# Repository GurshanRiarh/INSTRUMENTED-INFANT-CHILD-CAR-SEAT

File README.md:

# Instrumented Infant-Child Car Seat — Pressure-Sensitive Mat Hardware

This repository contains the KiCad hardware for the pressure-sensitive mat (PSM)
sub-system of the Carleton University capstone project **Instrumented
Infant-Child Car Seat**.

Two hardware revisions are included:

| Revision | Purpose | Board |
|---|---|---|
| **PSM V1** | Reproduction of Roger Selzler's 2018 thesis PSM (16× VCNL4020, 4×4 array). This is the experimental baseline. | 101.6 × 101.6 mm, 0.2 mm polyimide flex, 2 layers |
| **PSM V3** | Prannav's proposed improvements: VCNL4030X01 sensors, four factory I²C addresses per tile, one mux, modular 2×2 tiles, sealing/waterproofing features. | 4 × 30 × 30 mm flex tiles + 60 × 40 mm FR4 hub |

Both PCB revisions pass KiCad DRC with **0 violations and 0 unconnected
items**. All three schematics pass ERC with **0 violations**. The boards are
research prototypes, not certified medical or automotive devices.

**Interactive board viewer:** open [board-viewer.html](board-viewer.html) in a browser for 3D angled/top/bottom views, 2D copper/silkscreen views, full schematics, and a lightbox.

## Repository map

```
board-viewer.html            self-contained 3D + 2D board viewer
hardware/
  libraries/                 footprints, symbols, and approximate STEP models
  psm-v1/                    thesis-baseline KiCad project (schematic + PCB)
    fab/                     Gerbers, drill, position file, PDF/SVG preview
  psm-v3/
    tile/                    modular 4-sensor tile project (schematic + PCB)
    hub/                     one-mux / four-port hub project (schematic + PCB)
docs/                        architecture, design notes, validation, fabrication, tests
mechanical/                  parametric silicone tile mold (OpenSCAD) + process notes
scripts/                     board/3D/viewer generators, BOM and check helpers
firmware/                    optional I²C bring-up script for a Raspberry Pi
```

## Quick start

1. Install KiCad 9 or newer (this design was validated with **KiCad 10.0.7**).
2. Open one of:
   - `hardware/psm-v1/psm-v1.kicad_pro` — schematic + PCB
   - `hardware/psm-v3/tile/psm-v3-tile.kicad_pro` — sensor tile schematic + PCB
   - `hardware/psm-v3/hub/psm-v3-hub.kicad_pro` — hub schematic + PCB
3. The project-local `fp-lib-table` and `sym-lib-table` load the custom
   footprints/symbols from `hardware/libraries/`.
4. Fabrication data is in each project's `fab/` folder. Review the fab notes
   in [docs/fabrication.md](docs/fabrication.md) before ordering.

Command-line checks:

```bash
kicad-cli pcb drc --severity-all --output drc.rpt hardware/psm-v1/psm-v1.kicad_pcb
kicad-cli sch erc --output erc.rpt hardware/psm-v1/psm-v1.kicad_sch
kicad-cli pcb drc --severity-all --output drc.rpt hardware/psm-v3/tile/psm-v3-tile.kicad_pcb
kicad-cli sch erc --output erc.rpt hardware/psm-v3/tile/psm-v3-tile.kicad_sch
kicad-cli pcb drc --severity-all --output drc.rpt hardware/psm-v3/hub/psm-v3-hub.kicad_pcb
kicad-cli sch erc --output erc.rpt hardware/psm-v3/hub/psm-v3-hub.kicad_sch

# Regenerate the self-contained viewer from the current PCB/schematic files
python3 scripts/build_board_viewer.py
```

## PSM V1 — thesis baseline

The V1 board follows Selzler's thesis:

- 16 × **Vishay VCNL4020** infrared proximity sensors in a 4×4 grid on a
  4-inch-square flexible PCB.
- Two **PCA9548A** 8-channel I²C switches at 0x70 and 0x71. Each VCNL4020 has
  the fixed 7-bit address 0x13, so each sensor gets its own mux channel:
  - U17 channels 0–7 → U1–U8
  - U18 channels 0–7 → U9–U16
- 10 Ω IR-anode series resistors, 100 nF local decoupling per sensor,
  22 µF bulk per mux, 4.7 kΩ upstream I²C pull-ups, 10 kΩ reset/INT pull-ups.
- 2×5, 2.54 mm host header (Tiva/LaunchPad-compatible).
- 25.4 mm sensor pitch, 0.2 mm polyimide flex stack-up, 2 layers.

The editable schematic is `hardware/psm-v1/psm-v1.kicad_sch`; a PDF is at
[docs/psm-v1-schematic.pdf](docs/psm-v1-schematic.pdf).

> **Important:** the thesis does not publish a complete netlist, BOM, or
> mechanical drawing. The V1 design is a reconstruction from the thesis text
> and the Vishay datasheet. Verify the silicone cavity geometry against the
> original before fabrication.

## PSM V3 — modular, serviceable upgrade

V3 implements the improvement points from Prannav's proposal sections:

| Proposal point | Implementation |
|---|---|
| Replace the NRND VCNL4020 | **VCNL4030X01** (AEC-Q101, 16-bit PS, four factory addresses) |
| Reduce mux complexity / improve addressing | One **PCA9548A** (0x70) serves four tile ports; each tile has four sensors at 0x60/0x51/0x40/0x41. One mux supports up to 8 tiles / 32 sensors. |
| Do not restrict the array to 4×4 | Modular **2×2 sensor tiles** (30 × 30 mm) can be placed along the car-seat contour and replaced individually. |
| Waterproofing / infant environment | Sealing-ring guide on `Dwgs.User`, ground ring, via tenting/plugging option, ENIG finish, conformal-coat instructions, sealed connectors. |
| Silicone manufacturing | Parametric vacuum-degassing mold in `mechanical/tile_mold.scad` plus process notes. |
| KiCad design package | Full tile and hub PCB projects, BOM, Gerbers, drill, position files, PDF/SVG previews. |

| V3 tile PCB | V3 hub PCB |
|---|---|
|  |  |

| V3 tile schematic | V3 hub schematic |
|---|---|
|  |  |

The V3 projects include full schematics (`psm-v3-tile.kicad_sch` and
`psm-v3-hub.kicad_sch`), the connection topology diagram, and the routed PCBs.
Schematics are in [docs/psm-v3-tile-schematic.pdf](docs/psm-v3-tile-schematic.pdf)
and [docs/psm-v3-hub-schematic.pdf](docs/psm-v3-hub-schematic.pdf).

## Pinouts and address map

### V1 host header J1 (2×5, 2.54 mm)

| Pin | Net | Pin | Net |
|---:|---|---:|---|
| 1 | 3V3 | 2 | GND |
| 3 | SDA | 4 | SCL |
| 5 | INT_N | 6 | MUX_RST |
| 7 | 5V (optional) | 8 | GND |
| 9 | NC | 10 | NC |

### V1 sensor channel map

| Mux | Address | Channel 0 | 1 | 2 | 3 | 4 | 5 | 6 | 7 |
|---|---|---|---|---|---|---|---|---|---|
| U17 | 0x70 | U1 | U2 | U3 | U4 | U5 | U6 | U7 | U8 |
| U18 | 0x71 | U9 | U10 | U11 | U12 | U13 | U14 | U15 | U16 |

### V1 VCNL4020 pin use

| Pin | Name | Connection |
|---:|---|---|
| 1 | IR anode | 3V3 through 10 Ω; 100 nF to GND |
| 2 | SDA | Mux channel `SDA_Cn` |
| 3 | INT | `INT_N` (open-drain, 10 kΩ pull-up) |
| 4 | SCL | Mux channel `SCL_Cn` |
| 5 | VDD | 3V3; 100 nF to GND |
| 6, 7 | NC | Not connected |
| 8, 9 | GND | GND |
| 10 | IR cathode | Not connected (internal emitter) |

### V3 tile connector J1 (1×6, 1.27 mm)

| Pin | Net |
|---:|---|
| 1 | 3V3 |
| 2 | GND |
| 3 | SDA |
| 4 | SCL |
| 5 | INT_N |
| 6 | NC (future) |

### V3 tile sensor addresses

| Sensor | Order code | 7-bit address |
|---|---|---:|
| U1 | VCNL4030X01-GS08 | 0x60 |
| U2 | VCNL40301X01-GS08 | 0x51 |
| U3 | VCNL40302X01-GS08 | 0x40 |
| U4 | VCNL40303X01-GS08 | 0x41 |

### V3 hub ports

| Hub port | Mux channel | Tile |
|---|---|---|
| J2 | 0 | Tile 0 |
| J3 | 1 | Tile 1 |
| J4 | 2 | Tile 2 |
| J5 | 3 | Tile 3 |

Host header J1 uses the same pinout as V1. Each tile's IR cathode and LDR
pins are tied together per the VCNL4030X01 datasheet; the IR anode has a
22 µF + 100 nF network per tile and 100 nF per sensor.

## BOM and ordering

See [hardware/BOM.md](hardware/BOM.md) for consolidated BOMs and order codes.
Key notes:

- **VCNL4020** is marked "not for new designs" by Vishay. The V1 board is a
  thesis reproduction; use it for baseline experiments only.
- **VCNL4030X01** is ordered as **four different order codes** to obtain the
  four I²C addresses. Do not substitute a single code for all four tile
  positions.
- The V3 tile footprint omits the exposed pad (EP) to preserve 0.15 mm
  clearance at the QFN. Pin 3 (GND) provides the electrical ground. For a
  production thermal design, add an EP with a laser-cut stencil and a
  reflow-verified 0.1 mm clearance.
- The V1 PSM uses a 0.2 mm polyimide flex. Add stiffeners behind the
  connector and muxes for repeated insertion; this is not modeled in KiCad.

## Validation

| Check | Result |
|---|---|
| V1 PCB DRC | 0 violations, 0 unconnected |
| V1 schematic ERC | 0 violations |
| V3 tile PCB DRC | 0 violations, 0 unconnected |
| V3 tile schematic ERC | 0 violations |
| V3 hub PCB DRC | 0 violations, 0 unconnected |
| V3 hub schematic ERC | 0 violations |
| Schematic-to-PCB netlist | 0 mismatches (all 3 designs) |

Details and reproduction commands are in
[docs/validation.md](docs/validation.md).

## Fabrication, assembly, and testing

- [docs/fabrication.md](docs/fabrication.md) — stack-ups, finish, via
  tenting/plugging, conformal coating, sealing, silicone process.
- [docs/testing.md](docs/testing.md) — bring-up, I²C scan, pressure/linearity,
  respiration, flex, and vehicle test plan.
- [docs/design-notes.md](docs/design-notes.md) — assumptions, V1→V3 mapping,
  open issues.
- [mechanical/README.md](mechanical/README.md) — vacuum-degassing mold and
  silicone process.

## Status and limitations

**Implemented**

- Full V1 schematic and routed PCB.
- Full V3 tile and hub schematics and routed PCBs.
- Custom VCNL4020/VCNL4030X01 footprints, PSM symbol library, and approximate STEP models.
- Fabrication outputs, BOMs, and validation reports.
- Approximate STEP 3D models for the custom VCNL4020 and VCNL4030X01 packages, used for 3D renders in the board viewer.

**Not implemented / not validated**

- No boards have been fabricated or electrically tested.
- No firmware, sensor-fusion pipeline, or app code is included.
- No silicone samples, flex-bend fatigue, thermal, EMC, or crash-safety
  testing.
- No medical or automotive certification. The system is a research
  prototype and must not be used as a medical device or as a substitute for
  a certified child restraint.
- The V1 design is a reconstruction; the original thesis hardware may differ
  in mux part number, board outline, and silicone geometry.

## Sources and attribution

- R. C. D. G. Selzler, *Development of a Novel Pressure-Sensitive Mat Using
  Proximity Sensors*, M.A.Sc. thesis, Carleton University, 2018.
- Capstone proposal, *Instrumented Infant-Child Car Seat*, 2026
  (Prannav's PSM sections and the V3 improvement points).
- Vishay VCNL4020 and VCNL4030X01 datasheets; TI PCA9548A datasheet.

Third-party symbol/footprint attribution is in
[docs/attribution.md](docs/attribution.md). The reference PDFs are not
committed to this repository.

## License

Original hardware design files and documentation in this repository are
released under the MIT License (see `LICENSE`). Third-party KiCad library
elements retain their original licenses; see `docs/attribution.md`.

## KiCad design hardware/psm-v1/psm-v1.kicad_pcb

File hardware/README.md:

# Hardware projects

| Project | KiCad files | Fabrication |
|---|---|---|
| PSM V1 (thesis baseline) | `psm-v1/psm-v1.kicad_pro`, `.kicad_sch`, `.kicad_pcb` | `psm-v1/fab/` |
| PSM V3 sensor tile | `psm-v3/tile/psm-v3-tile.kicad_pro`, `.kicad_sch`, `.kicad_pcb` | `psm-v3/tile/fab/` |
| PSM V3 hub | `psm-v3/hub/psm-v3-hub.kicad_pro`, `.kicad_sch`, `.kicad_pcb` | `psm-v3/hub/fab/` |

For a browser overview of all three boards, open `../board-viewer.html`.

The shared libraries are in `libraries/`:

- `libraries/psm.pretty/` — custom footprints (`VCNL4020`, `VCNL4030X01`) plus
  the standard footprints copied into the project so the boards are
  self-contained.
- `libraries/psm-symbols.kicad_sym` — project symbols used by all three
  schematics.
- `libraries/psm.3dshapes/` — approximate STEP models for the custom
  VCNL4020 and VCNL4030X01 packages. A copy also lives in
  `psm-v3/libraries/psm.3dshapes/` so the `${KIPRJMOD}` path resolves from the
  V3 projects.

Each project has its own `fp-lib-table` and `sym-lib-table` with relative
paths, so opening the `.kicad_pro` file is enough.

## Reproducing the boards

The generators are kept in `../scripts/`. They were run inside the KiCad
Flatpak, for example:

```bash
flatpak run --command=python3 org.kicad.KiCad scripts/make_footprints.py
flatpak run --command=python3 org.kicad.KiCad scripts/build_v1.py
# route the exported .dsn with Freerouting, then:
flatpak run --command=python3 org.kicad.KiCad scripts/finish_v1.py
flatpak run --command=python3 org.kicad.KiCad scripts/build_schematic.py
flatpak run --command=python3 org.kicad.KiCad scripts/build_schematic_v3.py
flatpak run --command=python3 org.kicad.KiCad scripts/set_fab_options.py
flatpak run --command=python3 org.kicad.KiCad scripts/export_bom.py
```

Freerouting 2.5.0 was used for routing:

```bash
java -jar freerouting.jar -de psm-v1.dsn -do psm-v1.ses -mp 100 -mt 8
```

The `.dsn`/`.ses` files are intermediates and are not committed. The routed
`.kicad_pcb` files are committed.

## Validation

```bash
kicad-cli pcb drc --severity-all --output drc.rpt psm-v1/psm-v1.kicad_pcb
kicad-cli sch erc --output erc.rpt psm-v1/psm-v1.kicad_sch
kicad-cli pcb drc --severity-all --output drc.rpt psm-v3/tile/psm-v3-tile.kicad_pcb
kicad-cli sch erc --output erc.rpt psm-v3/tile/psm-v3-tile.kicad_sch
kicad-cli pcb drc --severity-all --output drc.rpt psm-v3/hub/psm-v3-hub.kicad_pcb
kicad-cli sch erc --output erc.rpt psm-v3/hub/psm-v3-hub.kicad_sch
```

Current result: 0 DRC violations and 0 unconnected items on all three PCBs;
0 ERC violations on all three schematics; 0 schematic-to-PCB netlist
mismatches (see `docs/validation.md`).

## Fabrication outputs

Each `fab/` folder contains:

- Gerbers: F.Cu, B.Cu, F.Mask, B.Mask, F.Silkscreen, Edge.Cuts
- Excellon drill files (PTH and NPTH)
- Pick-and-place CSV (`*-pos.csv`)
- PDF and SVG previews

*These are prototype files. Review the stack-up notes in
[docs/fabrication.md](../docs/fabrication.md) before ordering.*

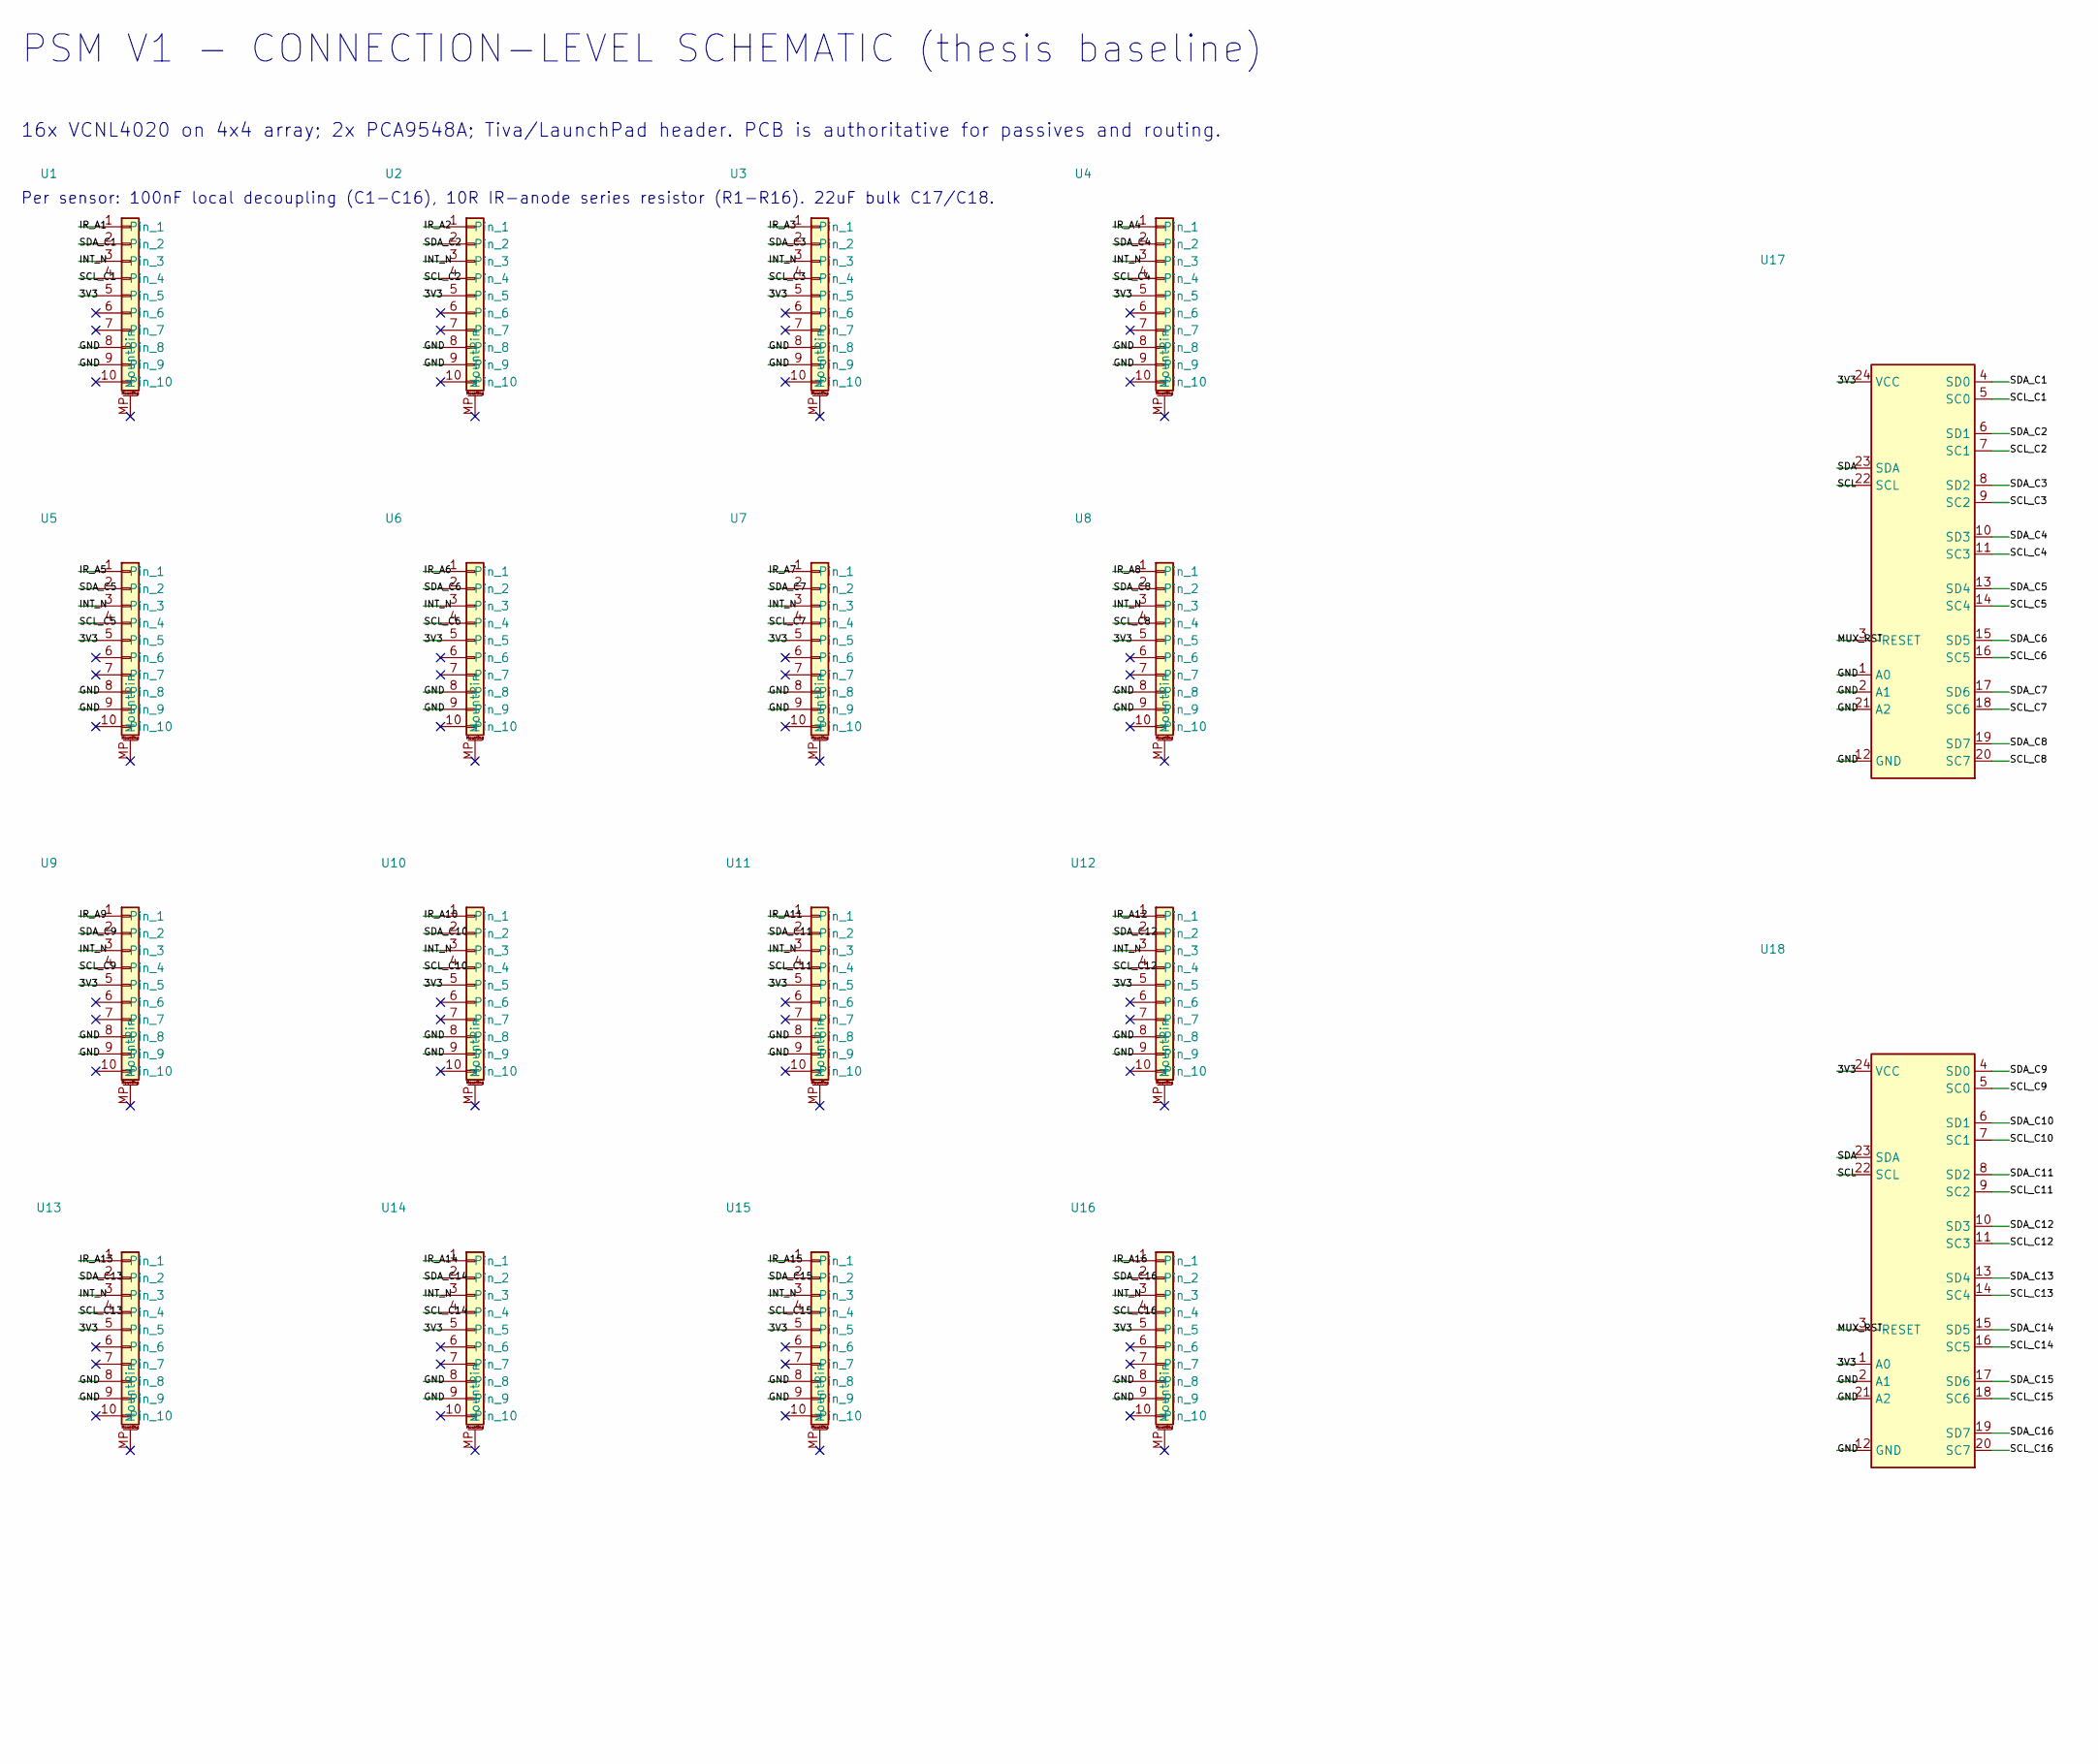
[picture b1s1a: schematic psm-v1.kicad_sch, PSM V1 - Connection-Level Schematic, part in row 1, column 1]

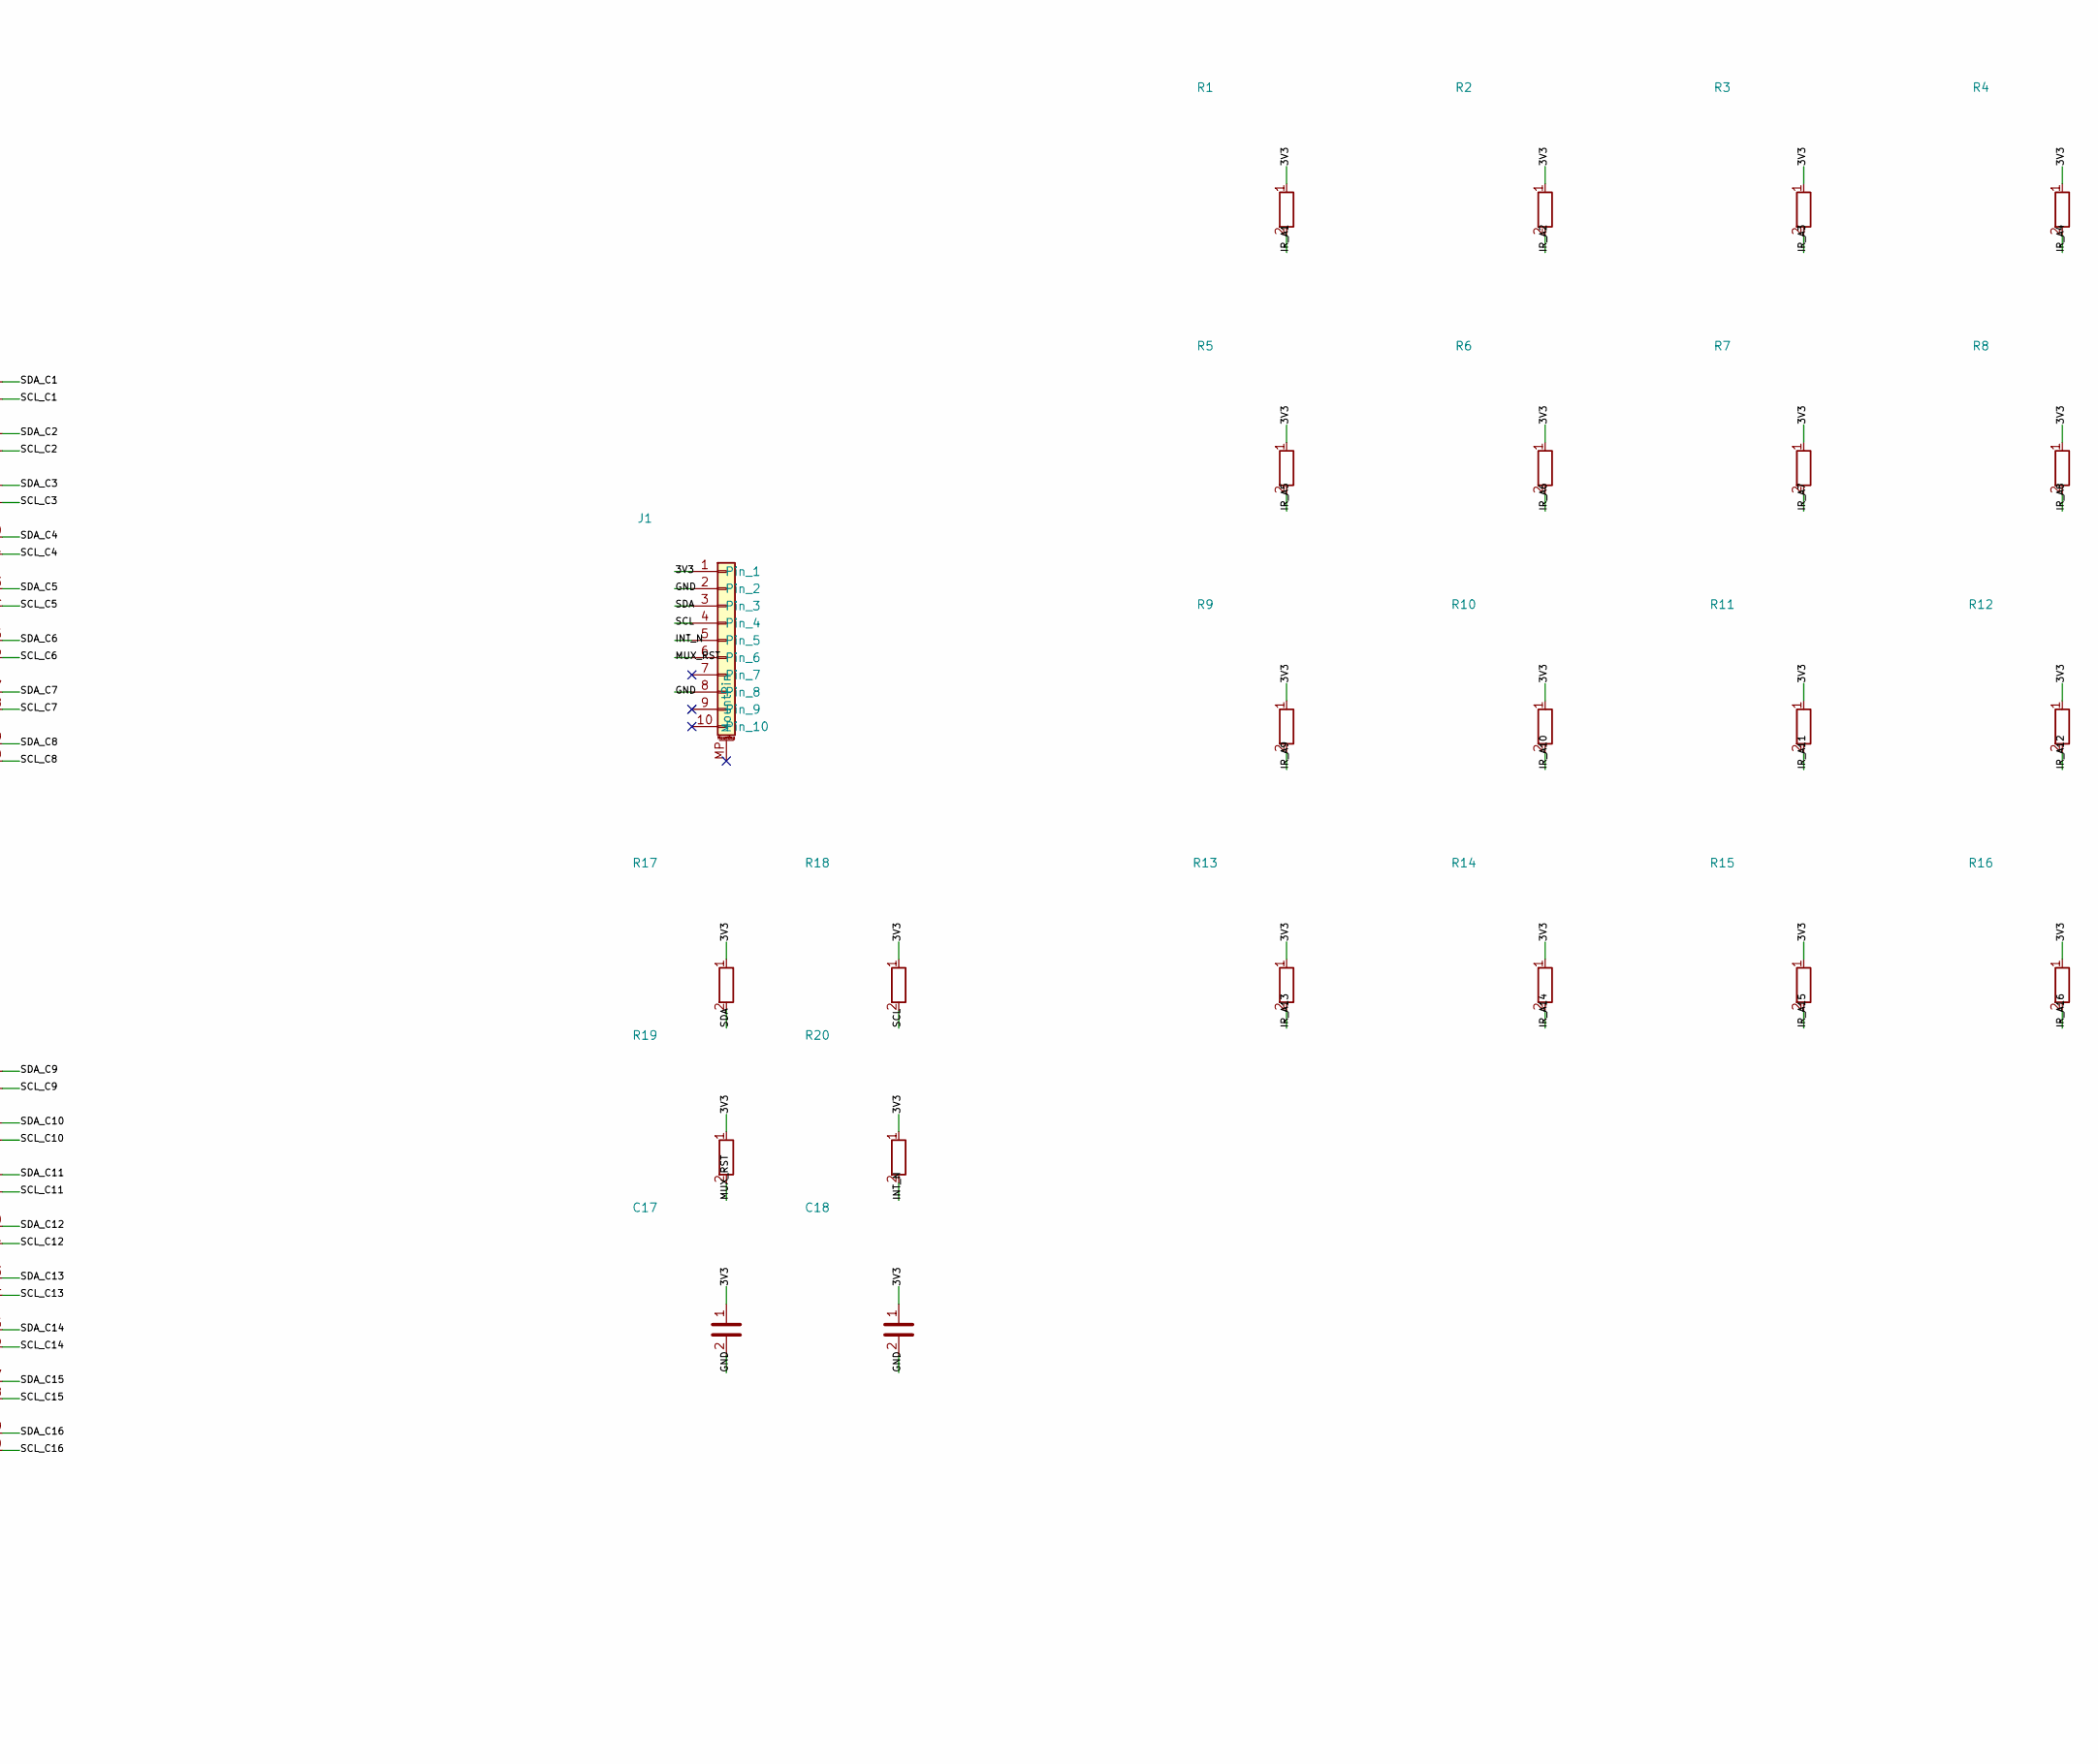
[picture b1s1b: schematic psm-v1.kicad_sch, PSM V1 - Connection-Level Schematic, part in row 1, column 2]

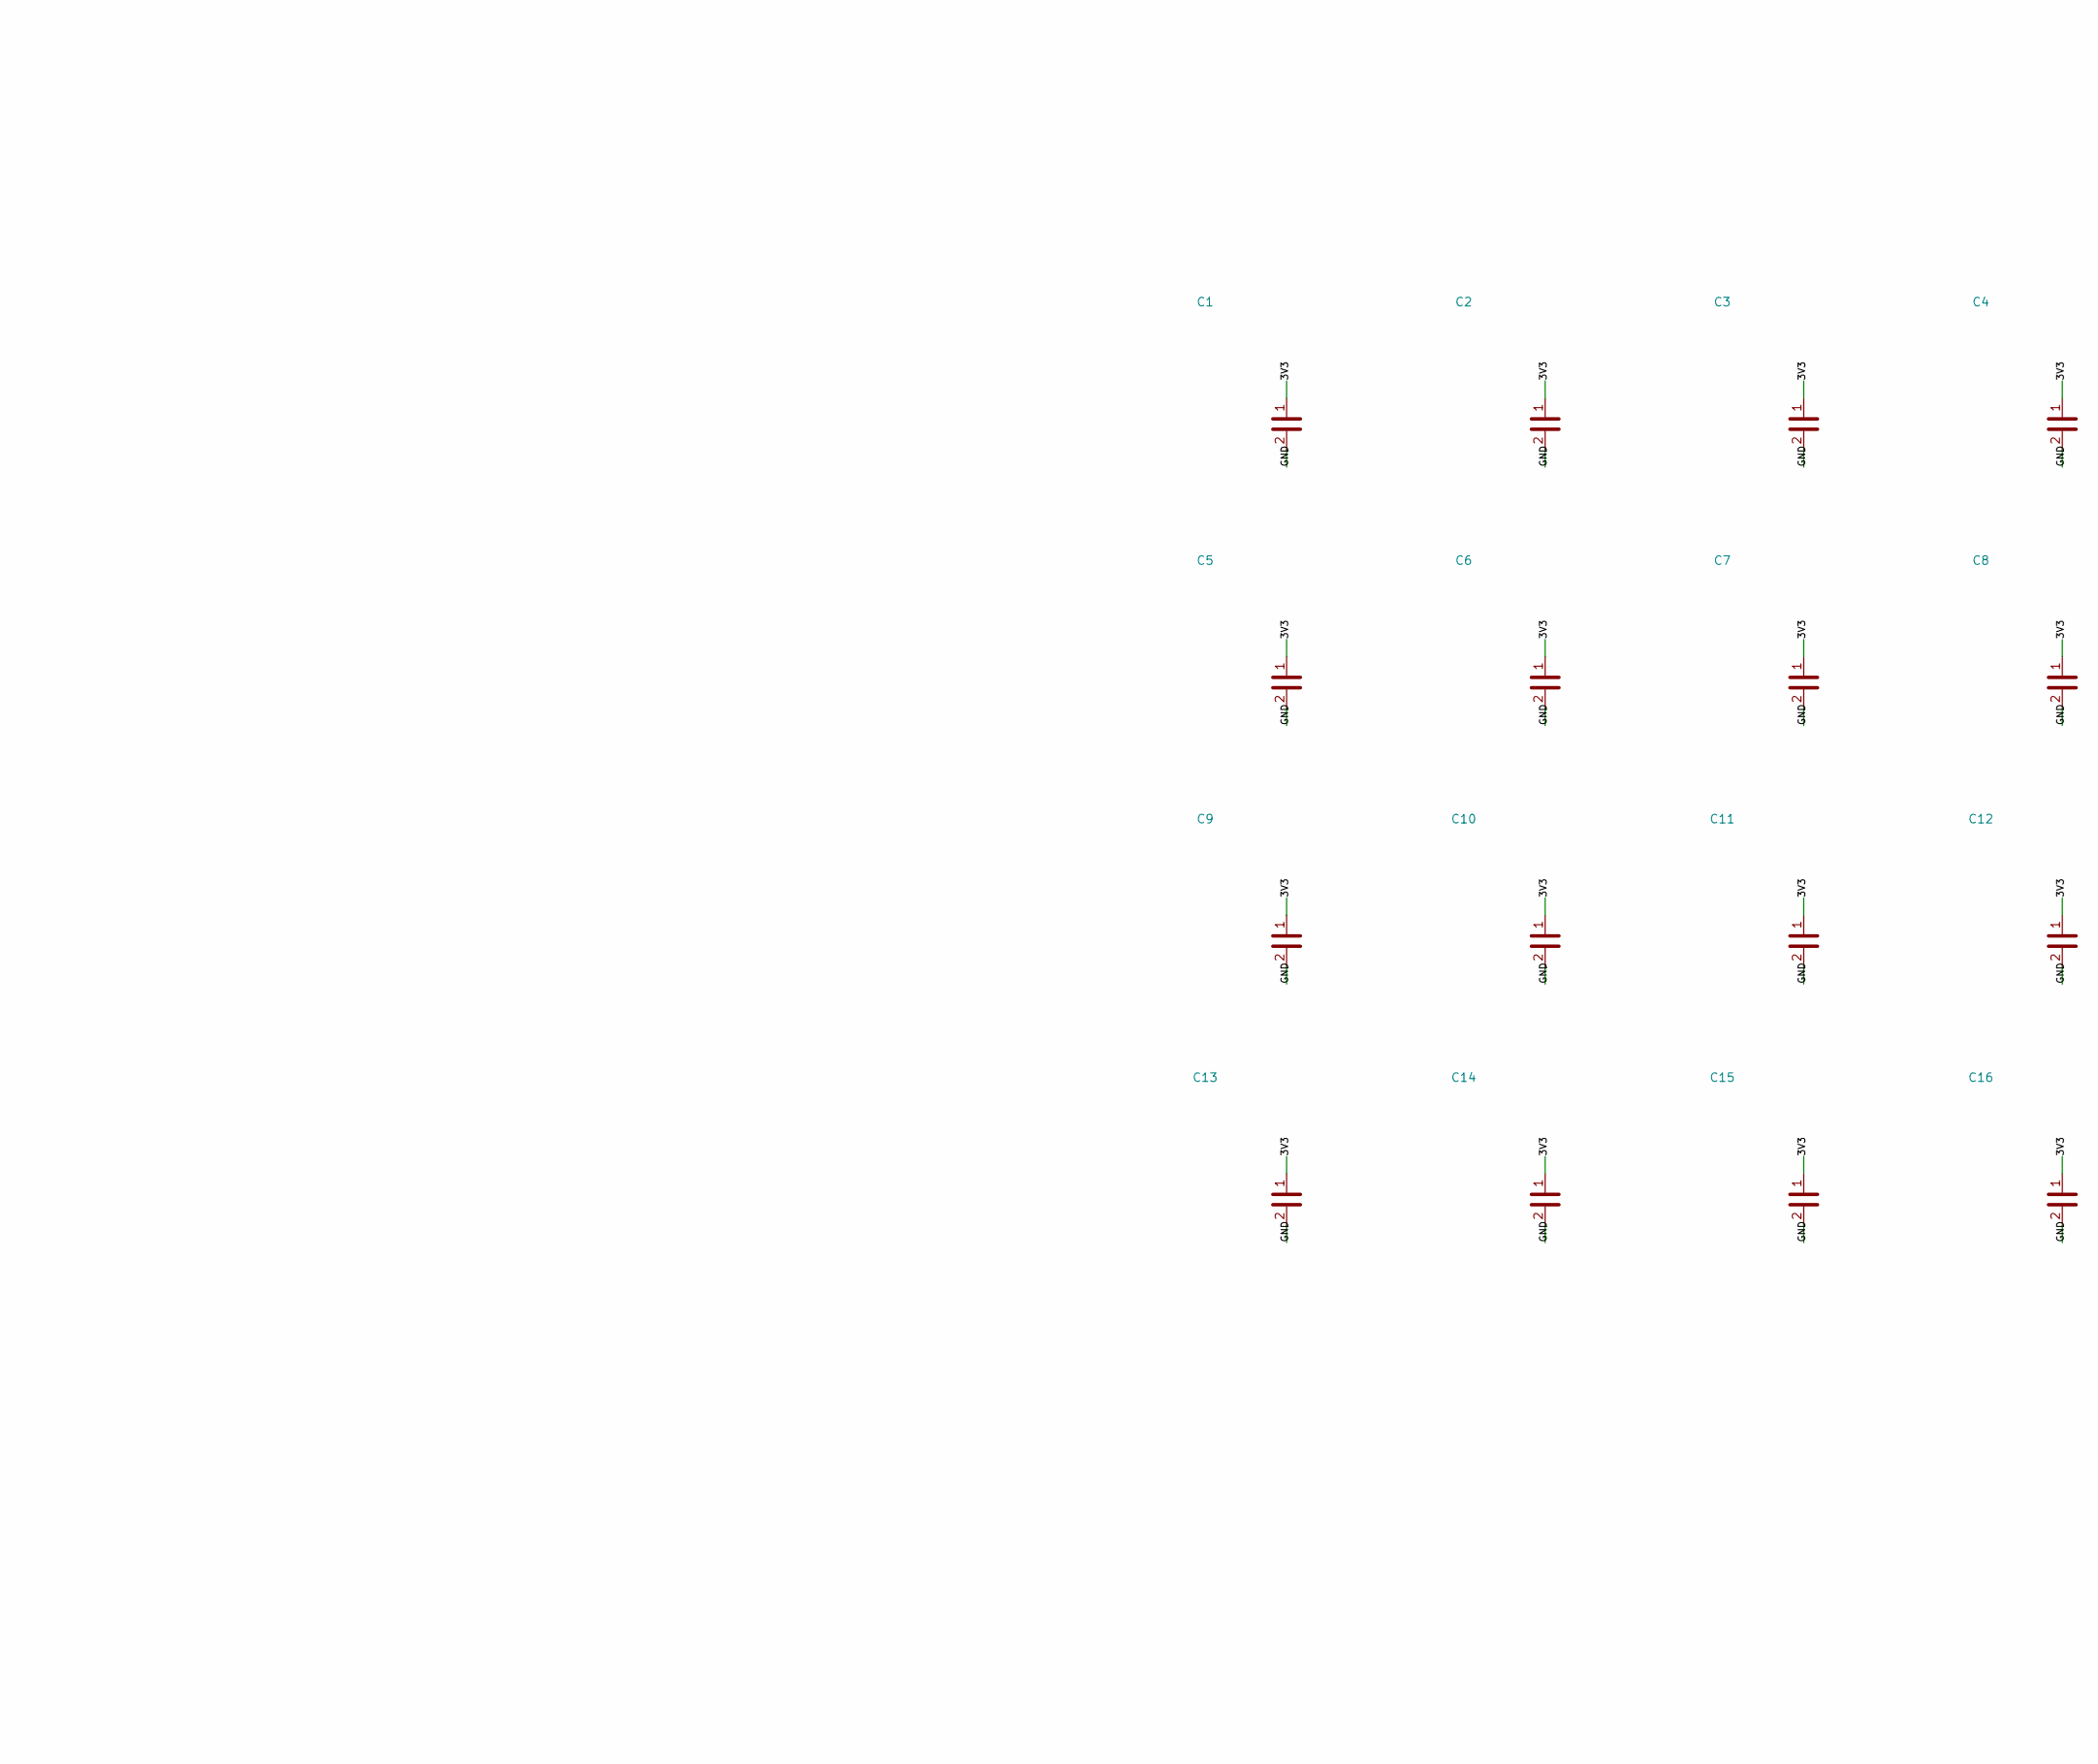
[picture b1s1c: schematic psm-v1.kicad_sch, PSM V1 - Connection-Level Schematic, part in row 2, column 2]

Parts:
C1, C2, C3, C4, C5, C6, C7, C8, C9, C10, C11, C12, C13, C14, C15, C16: 100n; C_0603_1608Metric; Part Description 0.1uF 10% 16V Ceramic Capacitor X7R 040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
C17, C18: 22u; C_0603_1608Metric; Part Description 0.1uF 10% 16V Ceramic Capacitor X7R 040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
J1: HOST_IF; PinHeader_2x05_P2.54mm_Vertical
R1, R2, R3, R4, R5, R6, R7, R8, R9, R10, R11, R12, R13, R14, R15, R16: 10R; R_0603_1608Metric
R17, R18: 4.7k; R_0603_1608Metric
R19, R20: 10k; R_0603_1608Metric
U1, U2, U3, U4, U5, U6, U7, U8, U9, U10, U11, U12, U13, U14, U15, U16: VCNL4020
U17: PCA9548A 0x70; TSSOP-24_4.4x7.8mm_P0.65mm; MPN PI4MSD5V9548AZDEX
U18: PCA9548A 0x71; TSSOP-24_4.4x7.8mm_P0.65mm; MPN PI4MSD5V9548AZDEX

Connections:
3V3: C1.1, C2.1, C3.1, C4.1, C5.1, C6.1, C7.1, C8.1, C9.1, C10.1, C11.1, C12.1, C13.1, C14.1, C15.1, C16.1, C17.1, C18.1, J1.1, R1.1, R2.1, R3.1, R4.1, R5.1, R6.1, R7.1, R8.1, R9.1, R10.1, R11.1, R12.1, R13.1, R14.1, R15.1, R16.1, R17.1, R18.1, R19.1, R20.1, U1.5, U2.5, U3.5, U4.5, U5.5, U6.5, U7.5, U8.5, U9.5, U10.5, U11.5, U12.5, U13.5, U14.5, U15.5, U16.5, U17.24 (VCC), U18.1 (A0), U18.24 (VCC); also elsewhere on the board
GND: C1.2, C2.2, C3.2, C4.2, C5.2, C6.2, C7.2, C8.2, C9.2, C10.2, C11.2, C12.2, C13.2, C14.2, C15.2, C16.2, C17.2, C18.2, J1.2, J1.8, U1.8, U1.9, U2.8, U2.9, U3.8, U3.9, U4.8, U4.9, U5.8, U5.9, U6.8, U6.9, U7.8, U7.9, U8.8, U8.9, U9.8, U9.9, U10.8, U10.9, U11.8, U11.9, U12.8, U12.9, U13.8, U13.9, U14.8, U14.9, U15.8, U15.9, U16.8, U16.9, U17.1 (A0), U17.2 (A1), U17.12 (GND), U17.21 (A2), U18.2 (A1), U18.12 (GND), U18.21 (A2); also elsewhere on the board
INT_N: J1.5, R20.2, U1.3, U2.3, U3.3, U4.3, U5.3, U6.3, U7.3, U8.3, U9.3, U10.3, U11.3, U12.3, U13.3, U14.3, U15.3, U16.3; also elsewhere on the board
IR_A1: R1.2, U1.1
IR_A2: R2.2, U2.1
IR_A3: R3.2, U3.1
IR_A4: R4.2, U4.1
IR_A5: R5.2, U5.1
IR_A6: R6.2, U6.1
IR_A7: R7.2, U7.1
IR_A8: R8.2, U8.1
IR_A9: R9.2, U9.1
IR_A10: R10.2, U10.1
IR_A11: R11.2, U11.1
IR_A12: R12.2, U12.1
IR_A13: R13.2, U13.1
IR_A14: R14.2, U14.1
IR_A15: R15.2, U15.1
IR_A16: R16.2, U16.1
MUX_RST: J1.6, R19.2, U17.3 (~RESET), U18.3 (~RESET)
SCL: J1.4, R18.2, U17.22 (SCL), U18.22 (SCL); also elsewhere on the board
SCL_C1: U1.4, U17.5 (SC0)
SCL_C2: U2.4, U17.7 (SC1)
SCL_C3: U3.4, U17.9 (SC2)
SCL_C4: U4.4, U17.11 (SC3)
SCL_C5: U5.4, U17.14 (SC4)
SCL_C6: U6.4, U17.16 (SC5)
SCL_C7: U7.4, U17.18 (SC6)
SCL_C8: U8.4, U17.20 (SC7)
SCL_C9: U9.4, U18.5 (SC0)
SCL_C10: U10.4, U18.7 (SC1)
SCL_C11: U11.4, U18.9 (SC2)
SCL_C12: U12.4, U18.11 (SC3)
SCL_C13: U13.4, U18.14 (SC4)
SCL_C14: U14.4, U18.16 (SC5)
SCL_C15: U15.4, U18.18 (SC6)
SCL_C16: U16.4, U18.20 (SC7)
SDA: J1.3, R17.2, U17.23 (SDA), U18.23 (SDA); also elsewhere on the board
SDA_C1: U1.2, U17.4 (SD0)
SDA_C2: U2.2, U17.6 (SD1)
SDA_C3: U3.2, U17.8 (SD2)
SDA_C4: U4.2, U17.10 (SD3)
SDA_C5: U5.2, U17.13 (SD4)
SDA_C6: U6.2, U17.15 (SD5)
SDA_C7: U7.2, U17.17 (SD6)
SDA_C8: U8.2, U17.19 (SD7)
SDA_C9: U9.2, U18.4 (SD0)
SDA_C10: U10.2, U18.6 (SD1)
SDA_C11: U11.2, U18.8 (SD2)
SDA_C12: U12.2, U18.10 (SD3)
SDA_C13: U13.2, U18.13 (SD4)
SDA_C14: U14.2, U18.15 (SD5)
SDA_C15: U15.2, U18.17 (SD6)
SDA_C16: U16.2, U18.19 (SD7)

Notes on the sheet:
PSM V1 - CONNECTION-LEVEL SCHEMATIC (thesis baseline)
16x VCNL4020 on 4x4 array; 2x PCA9548A; Tiva/LaunchPad header. PCB is authoritative for passives and routing.
Per sensor: 100nF local decoupling (C1-C16), 10R IR-anode series resistor (R1-R16). 22uF bulk C17/C18.
U17 channels 0-7 -> U1..U8; U18 channels 0-7 -> U9..U16.
VCNL4020: 1 IR anode, 2 SDA, 3 INT, 4 SCL, 5 VDD, 8/9 GND, 6/7/10 NC.

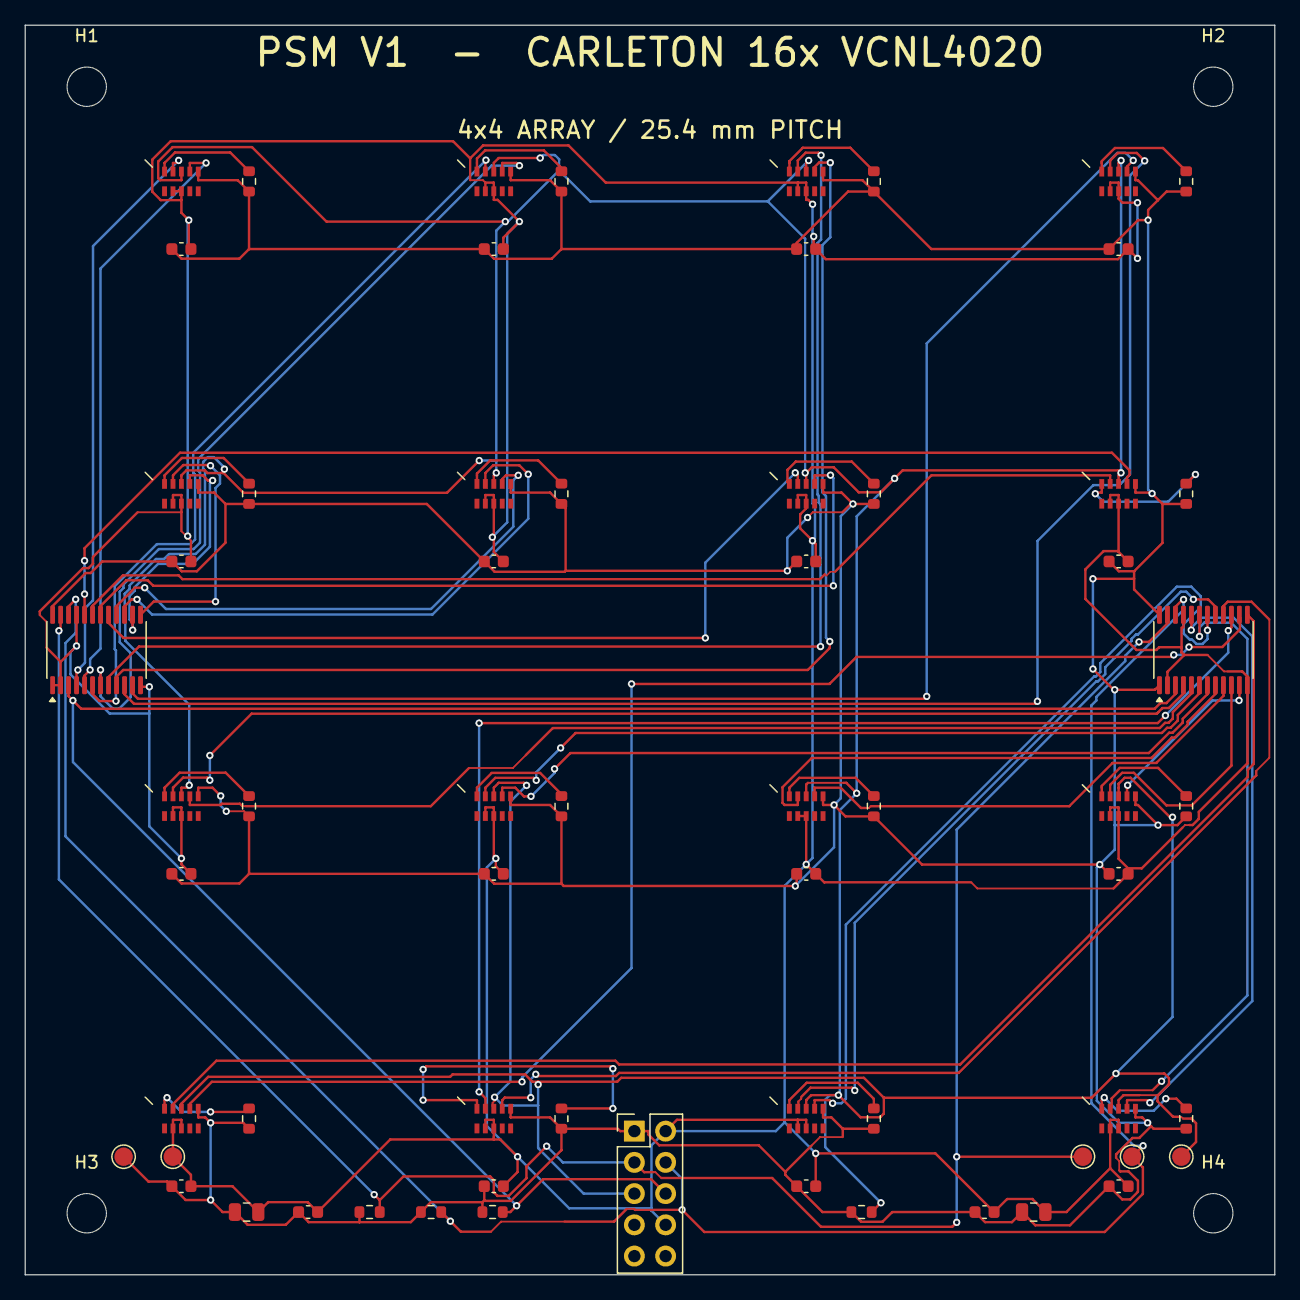
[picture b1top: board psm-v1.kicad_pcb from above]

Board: 2 copper layers, 101.6 x 101.6 mm, 68 parts (0 on the bottom side), 54 nets.

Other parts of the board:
C19, C20: 100n; C_0603_1608Metric
H1, H2, H3, H4: M3; MountingHole_3.2mm_M3
TP1: 3V3; TestPoint_Pad_D1.5mm
TP2: GND; TestPoint_Pad_D1.5mm
TP3: SDA; TestPoint_Pad_D1.5mm
TP4: SCL; TestPoint_Pad_D1.5mm
TP5: INT_N; TestPoint_Pad_D1.5mm

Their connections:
3V3: C19.1, C20.1, TP1.1; also elsewhere on the board
GND: C19.2, C20.2, TP2.1; also elsewhere on the board
INT_N: TP5.1; also elsewhere on the board
SCL: TP4.1; also elsewhere on the board
SDA: TP3.1; also elsewhere on the board

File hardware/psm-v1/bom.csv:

Quantity,References,Value,Footprint
18,C1 C10 C11 C12 C13 C14 C15 C16 C19 C2 C20 C3 C4 C5 C6 C7 C8 C9,100n,C_0603_1608Metric
16,R1 R10 R11 R12 R13 R14 R15 R16 R2 R3 R4 R5 R6 R7 R8 R9,10R,R_0603_1608Metric
2,R19 R20,10k,R_0603_1608Metric
2,C17 C18,22u,C_0805_2012Metric
1,TP1,3V3,TestPoint_Pad_D1.5mm
2,R17 R18,4.7k,R_0603_1608Metric
1,TP2,GND,TestPoint_Pad_D1.5mm
1,TP5,INT_N,TestPoint_Pad_D1.5mm
4,H1 H2 H3 H4,M3,MountingHole_3.2mm_M3
2,U17 U18,PCA9548A,TSSOP-24_4.4x7.8mm_P0.65mm
1,TP4,SCL,TestPoint_Pad_D1.5mm
1,TP3,SDA,TestPoint_Pad_D1.5mm
1,J1,Tiva_IF,PinHeader_2x05_P2.54mm_Vertical
16,U1 U10 U11 U12 U13 U14 U15 U16 U2 U3 U4 U5 U6 U7 U8 U9,VCNL4020,VCNL4020

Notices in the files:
parts and their libraries:
License: Apache-2.0
